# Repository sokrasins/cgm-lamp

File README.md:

# CGM Lamp

An ESP32-C6-powered device to indicate glucose as a color

- `/pcb` - KiCAD PCB design
- `/code` - Rust firmware project
- `/stl` - Models for the lamp housing

## Features

- ✅ Displays glucose via lamp color
- ✅ Max brightness settable by rotating lamp body
- ✅ Device configuration through web server
  - ✅ Wifi credentials
  - ✅ Dexcom credentials
  - ✅ Device settings
- Non-volatile storage of critical device settings
  - ✅ Store mission-critical device settings
  - At-rest encryption
- ✅ AP Mode when device can't connect or has no credentials
- REST API for automated control of device settings
  - ✅ Home Assistant compatible
  - TLS
- ✅ Included battery, allows fully-wireless operation
  - ✅ Operation with battery optional
  - Indicators for:
    - ✅ Remaining capacity
    - Charge state
- ✅ USB-C port for charging and debug
  - ✅ Provides both debug console and power/charge
- Re-flash as a generic ESPHome device
- ✅ Optional terminal to extend Neopixel configuration

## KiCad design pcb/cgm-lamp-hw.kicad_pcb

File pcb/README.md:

# CGM Lamp Hardware

The PCB for the CGM lamp

## BOM
[IBOM](https://htmlpreview.github.io/?https://github.com/sokrasins/cgm-lamp/blob/main/pcb/bom/ibom.html)

## To Do

- Fix usb D+ and D-, move encoder button pin
- Add current measurement header
  - battery, usb, 3V3
- Move buttons away from board edge
- Smaller power switch
- Better silk screen, with functional button labels
- ESP pin for fuel gauge alert
- Increase current capacity of power block
- Low-voltage cut-off?
- Don't need reset button?
- Move USB so it's flush with housing
- Replace R5 with divider, to 3V3 so ESP can sense USB power

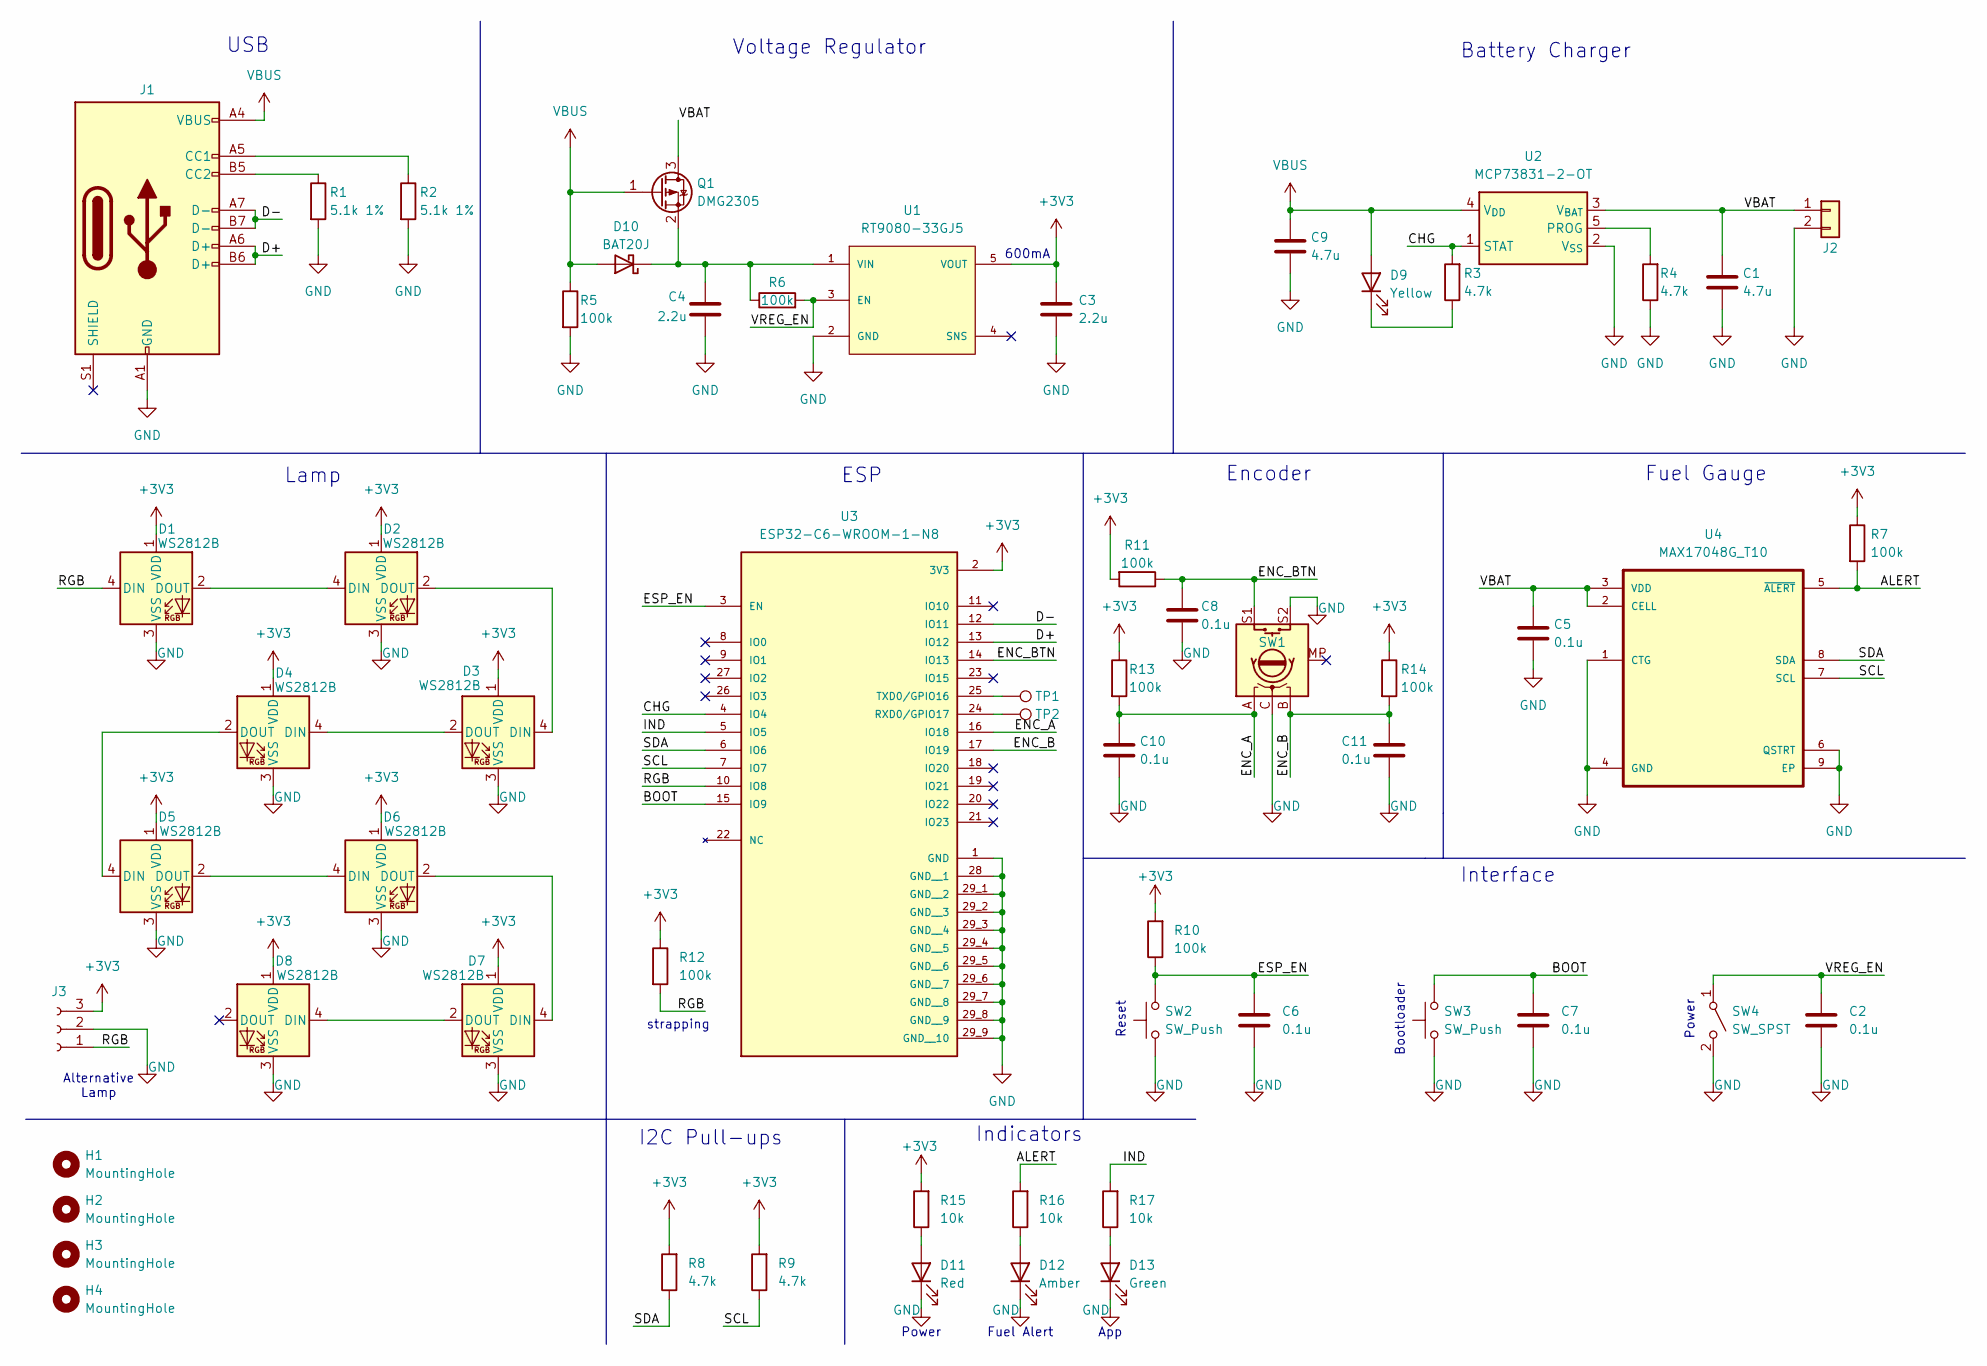
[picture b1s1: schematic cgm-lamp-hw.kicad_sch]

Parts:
C1, C9: 4.7u; C_0603_1608Metric_Pad1.08x0.95mm_HandSolder
C2, C5, C6, C7, C8, C10, C11: 0.1u; C_0603_1608Metric_Pad1.08x0.95mm_HandSolder
C3, C4: 2.2u; C_0603_1608Metric_Pad1.08x0.95mm_HandSolder
D1, D2, D3, D4, D5, D6, D7, D8: WS2812B; LED_WS2812B_PLCC4_5.0x5.0mm_P3.2mm
D9: Yellow; LED_1206_3216Metric_Pad1.42x1.75mm_HandSolder
D10: BAT20J; D_SOD-323_HandSoldering
D11: Red; LED_1206_3216Metric_Pad1.42x1.75mm_HandSolder
D12: Amber; LED_1206_3216Metric_Pad1.42x1.75mm_HandSolder
D13: Green; LED_1206_3216Metric_Pad1.42x1.75mm_HandSolder
H1, H2, H3, H4: MountingHole
J1: USB_C_Receptacle_USB2.0_14P; USB_C_Receptacle_GCT_USB4105-xx-A_16P_TopMnt_Horizontal
J2: Conn_01x02; JST_PH_S2B-PH-SM4-TB_1x02-1MP_P2.00mm_Horizontal
J3: DNP; PinHeader_1x03_P2.54mm_Vertical
Q1: DMG2305; SOT-23
R1, R2: 5.1k 1%; R_0603_1608Metric_Pad0.98x0.95mm_HandSolder
R3, R4, R8, R9: 4.7k; R_0603_1608Metric_Pad0.98x0.95mm_HandSolder
R5, R6, R7, R10, R11, R12, R13, R14: 100k; R_0603_1608Metric_Pad0.98x0.95mm_HandSolder
R15, R16, R17: 10k; R_0603_1608Metric_Pad0.98x0.95mm_HandSolder
SW1: RotaryEncoder_Switch_MP; RotaryEncoder_Bourns_Vertical_PEC12R-3x17F-Sxxxx
SW2, SW3: SW_Push; SW_SPST_PTS645
SW4: SW_SPST; SW_E-Switch_EG2219_DPDT_Angled
TP1, TP2: TestPoint; TestPoint_Loop_D2.54mm_Drill1.5mm_Beaded
U1: RT9080-33GJ5; SOT94P280X100-5N; Mouser_Part_Number 835-RT9080-33GJ5
U2: MCP73831-2-OT; SOT-23-5
U3: ESP32-C6-WROOM-1-N8; XCVR_ESP32-C6-WROOM-1-N8; PARTREV 1.0
U4: MAX17048G_T10; SON50P200X200X80-9N

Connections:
+3V3: C3.1, D1.1 (VDD), D2.1 (VDD), D3.1 (VDD), D4.1 (VDD), D5.1 (VDD), D6.1 (VDD), D7.1 (VDD), D8.1 (VDD), J3.3, R7.1, R8.2, R9.2, R10.2, R11.2, R12.1, R13.1, R14.1, R15.2, U1.5 (VOUT), U3.2 (3V3)
/ALERT: R7.2, R16.2, U4.5 (~ALERT)
/BOOT: C7.1, SW3.2, U3.15 (IO9)
/CHG: R3.2, U2.1 (STAT), U3.4 (IO4)
/D+: J1.A6 (D+), J1.B6 (D+), U3.13 (IO12)
/D-: J1.A7 (D-), J1.B7 (D-), U3.12 (IO11)
/ENC_A: C10.2, R13.2, SW1.A, U3.16 (IO18)
/ENC_B: C11.2, R14.2, SW1.B, U3.17 (IO19)
/ENC_BTN: C8.2, R11.1, SW1.S1, U3.14 (IO13)
/ESP_EN: C6.1, R10.1, SW2.2, U3.3 (EN)
/IND: R17.2, U3.5 (IO5)
/RGB: D1.4 (DIN), J3.1, R12.2, U3.10 (IO8)
/SCL: R9.1, U3.7 (IO7), U4.7 (SCL)
/SDA: R8.1, U3.6 (IO6), U4.8 (SDA)
/VBAT: C1.1, C5.1, J2.1, Q1.3 (D), U2.3 (V_{BAT}), U4.2 (CELL), U4.3 (VDD)
/VREG_EN: C2.1, R6.2, SW4.1 (A), U1.3 (EN)
GND: C1.2, C2.2, C3.2, C4.2, C5.2, C6.2, C7.2, C8.1, C9.2, C10.1, C11.1, D1.3 (VSS), D2.3 (VSS), D3.3 (VSS), D4.3 (VSS), D5.3 (VSS), D6.3 (VSS), D7.3 (VSS), D8.3 (VSS), D11.1 (K), D12.1 (K), D13.1 (K), J1.A1 (GND), J1.A12 (GND), J1.B1 (GND), J1.B12 (GND), J2.2, J3.2, R1.2, R2.2, R4.1, R5.2, SW1.C, SW1.S2, SW2.1, SW3.1, SW4.2 (B), U1.2 (GND), U2.2 (V_{SS}), U3.1 (GND), U3.28 (GND__1), U3.29_1 (GND__2), U3.29_2 (GND__3), U3.29_3 (GND__4), U3.29_4 (GND__5), U3.29_5 (GND__6), U3.29_6 (GND__7), U3.29_7 (GND__8), U3.29_8 (GND__9), U3.29_9 (GND__10), U4.1 (CTG), U4.4 (GND), U4.6 (QSTRT), U4.9 (EP)
unnamed: D1.2 (DOUT), D2.4 (DIN)
unnamed: D2.2 (DOUT), D3.4 (DIN)
unnamed: D3.2 (DOUT), D4.4 (DIN)
unnamed: D4.2 (DOUT), D5.4 (DIN)
unnamed: D5.2 (DOUT), D6.4 (DIN)
unnamed: D6.2 (DOUT), D7.4 (DIN)
unnamed: D7.2 (DOUT), D8.4 (DIN)
unnamed: D9.1 (K), R3.1
unnamed: C4.1, D10.1 (K), Q1.2 (S), R6.1, U1.1 (VIN)
unnamed: D11.2 (A), R15.1
unnamed: D12.2 (A), R16.1
unnamed: D13.2 (A), R17.1
unnamed: J1.A5 (CC1), R2.1
unnamed: J1.B5 (CC2), R1.1
unnamed: R4.2, U2.5 (PROG)
unnamed: TP2.1, U3.24 (RXD0/GPIO17)
unnamed: TP1.1, U3.25 (TXD0/GPIO16)
VBUS: C9.1, D9.2 (A), D10.2 (A), J1.A4 (VBUS), J1.A9 (VBUS), J1.B4 (VBUS), J1.B9 (VBUS), Q1.1 (G), R5.1, U2.4 (V_{DD})

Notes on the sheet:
strapping
Power
Indicators
Reset
Bootloader
600mA
I2C Pull-ups
Fuel Alert
USB
Interface
ESP
Voltage Regulator
App
Alternative Lamp
Battery Charger
Encoder
Lamp
Fuel Gauge

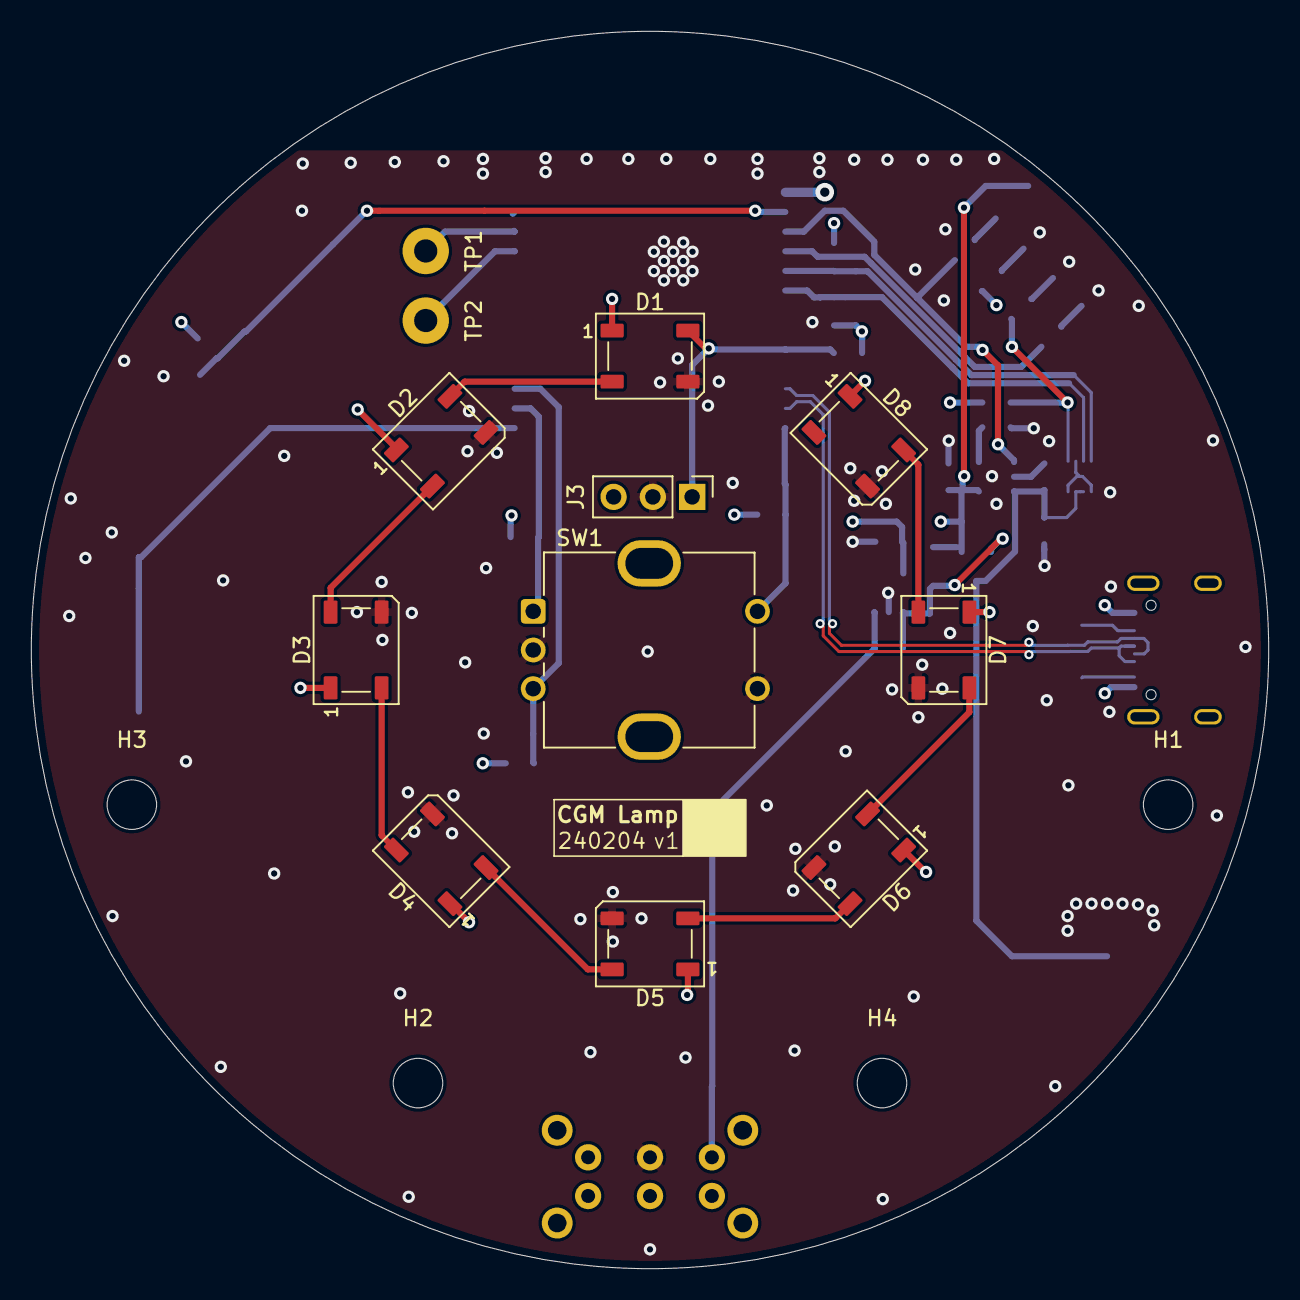
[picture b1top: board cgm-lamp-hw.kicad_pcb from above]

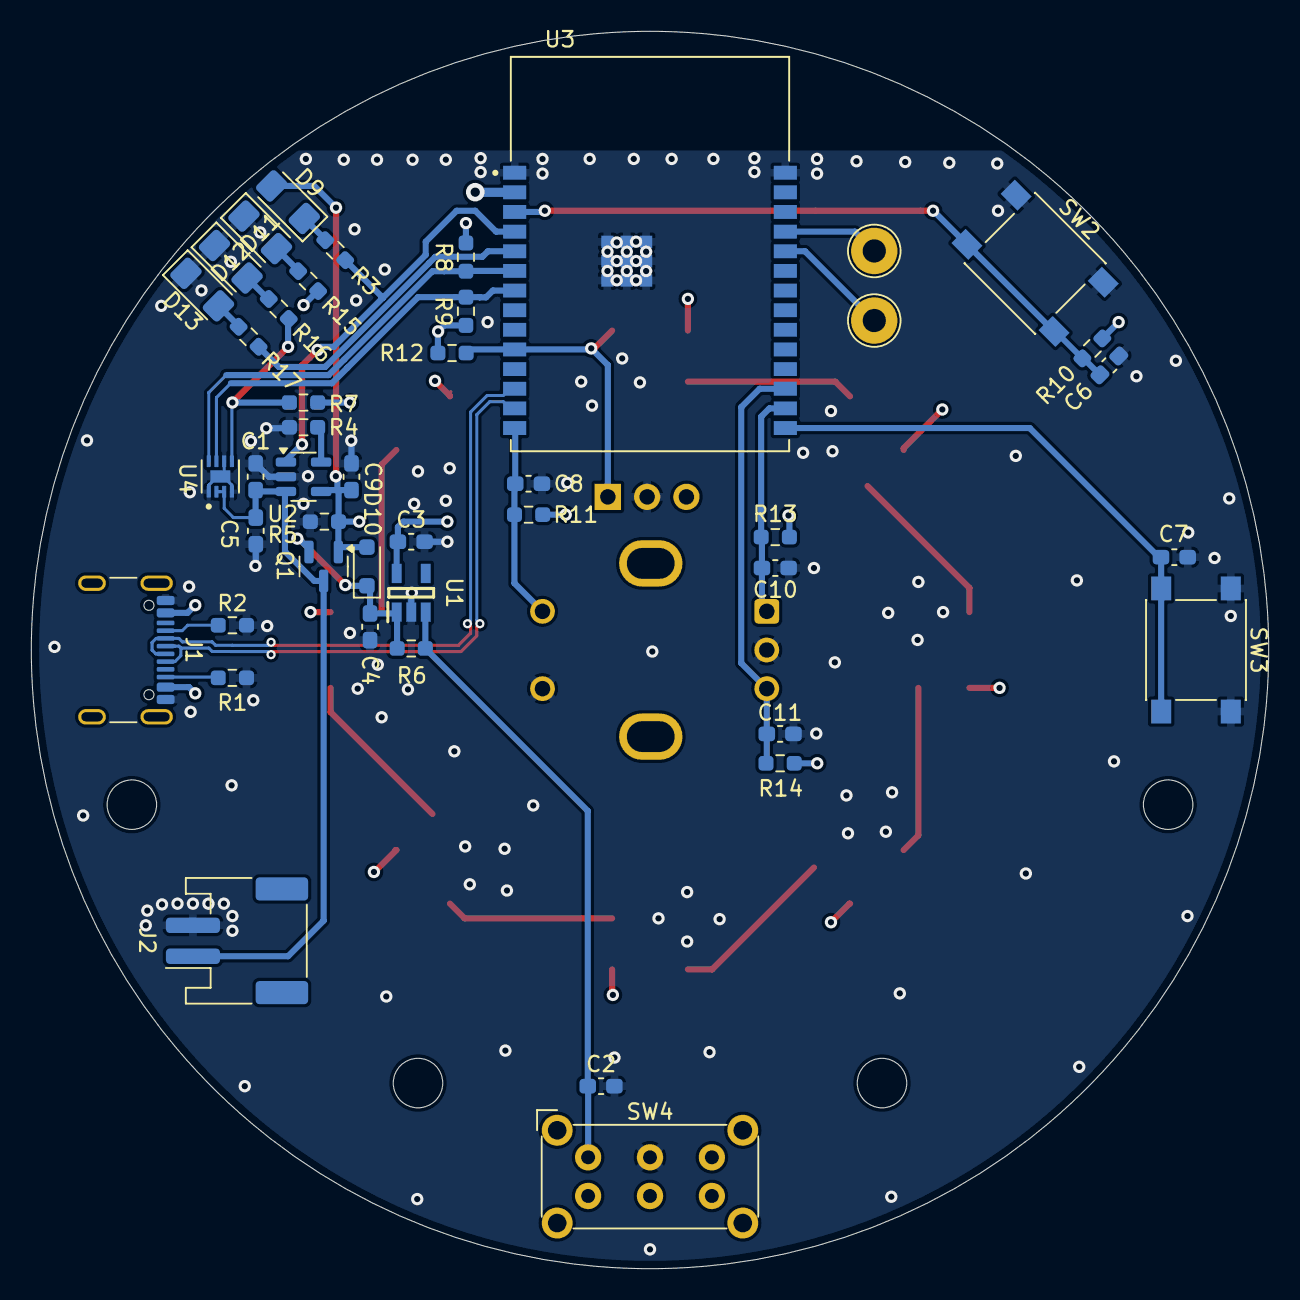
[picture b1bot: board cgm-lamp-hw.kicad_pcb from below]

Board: 4 copper layers, 80.0 x 80.0 mm, 59 parts (45 on the bottom side), 35 nets.

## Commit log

2025-01-22 Move rgb led back into it's own lib
2025-01-22 Factor out dexcom stuff into it's own file
2025-01-22 No warnings
2025-01-23 RUn LED update in a thread
2025-01-23 Clean up
2025-01-23 Try different colormaps
2025-01-23 Comments
2025-01-26 State machine in main
2025-01-26 Clean, add wifi check
2025-01-27 try server
2025-01-27 Mpre refactor
2025-01-27 Server scope is easier now, served settings page is styled a bit more
2025-01-27 Titles
2025-01-27 Adding settings concept
2025-01-27 readme
2025-01-27 Real settings from JSON
2025-01-28 Observer pattern
2025-01-28 Faster superloop
2025-01-28 finally link brightness to led state
2025-01-28 brightness setting is decent from web app
2025-01-29 save
2025-01-29 Change API path
2025-01-30 Add non-volatile storage
2025-01-30 top-level org
2025-01-30 Add kicad project
2025-01-30 Change dir names, pretty readme
2025-01-30 Assign footprints, start layout
2025-01-31 some layout
2025-01-31 Add AP mode and reset api
2025-01-31 transition to AP after too many unsuccessful wifi connection attempts
2025-01-31 Revert to AP if wifi connection fails too many times
2025-02-01 mdns
2025-02-01 Start to pull out wifi
2025-02-01 wifi in it's own module now
2025-02-01 Small cleanup
2025-02-01 move store into settings, change to ap_psk, change to brightness
2025-02-01 More layout
2025-02-03 layout
2025-02-03 Add dru, more layout
2025-02-03 Put in status response JSON
2025-02-04 Tweak footprints for drc, route USB
2025-02-05 Added ground vias
2025-02-05 Added moutning holes
2025-02-05 Change via sizes to meet jlc min
2025-02-05 Add panel prod files
2025-02-06 axum
2025-02-24 Add ibom
2025-02-24 Add link
2025-03-03 Handle case if no nvm settings stored yet
2025-03-03 Added title
2025-03-03 Bump rev, fix usb pin assignment
2025-03-03 Add an encoder
2025-03-03 hard-coded the number of LEDs. Make this dynamic
2025-03-03 Added todo list in README
2025-03-04 Added some really dumb encoder action
2025-03-04 faster led updates
2025-03-04 Add some simple fuel gasuge interactions
2025-03-04 Log fuel
2025-03-04 start basic gpio pins
2025-03-04 Added todo's
2025-03-05 Better dimmer action
2025-03-05 Update docu
2025-03-05 Added TODO
2025-03-06 Crappy encoder button handling
2025-03-06 add on state to lamp
2025-03-06 Add stls for the housing
2025-03-06 todos
2025-03-06 fix url
2025-03-06 link to render html
2025-03-06 finally fix bom link
2025-03-07 Refactoring data model'
2025-03-07 Collapse encoder and dimmer
2025-03-07 Working on server
2025-03-08 Refactor server start
2025-03-11 Change server state mechanism
2025-03-11 Put more stuff in it's own file, work on non-volatile saving again
2025-03-11 Handle reset request from server
2025-03-11 shorver nvs keys
2025-03-25 Constrain lamp brightness
2025-03-26 Forgot to add brightness cap back
2025-03-26 Add uptime and battery state to hosted page
2025-03-27 Styling
